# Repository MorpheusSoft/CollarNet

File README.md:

# 🐄 CollarNet / COWAI

**Ecosistema IoT Integral de Cerca Virtual, Telemetría Satelital y Monitoreo Ganadero en Tiempo Real**

---

## 📌 Descripción General

**CollarNet** (marca comercial **COWAI**) es una plataforma ganadera inteligente diseñada para entornos de campo y alta exigencia agropecuaria. Integra hardware IoT con geolocalización GNSS de alta precisión, comunicación celular 4G LTE, cercas virtuales poligonales dinámicas, acelerometría para monitoreo de actividad/rumia y una suite multiplataforma para técnicos y supervisores de finca.

---

## 🏗️ Arquitectura del Sistema

```
                   ┌──────────────────────────────────────────────┐
                   │               Collar IoT                     │
                   │    (ESP32-S3 + SIM7670G 4G LTE Digitel)     │
                   │  - GNSS Satelital (Lat/Lon en tiempo real)   │
                   │  - Algoritmo de Geocerca Ray-Casting Local   │
                   │  - Acelerómetro IMU (Reposo / Movimiento)    │
                   │  - Zumbador Piezoeléctrico (Alertas de Cerca)│
                   └──────────────────────┬───────────────────────┘
                                          │ MQTT (4G LTE Móvil)
                                          ▼
                   ┌──────────────────────────────────────────────┐
                   │             Broker MQTT Privado              │
                   │            (HiveMQ / Mosquitto)              │
                   └──────────────────────┬───────────────────────┘
                                          │
                                          ▼
┌─────────────────────────────────────────────────────────────────────────────────┐
│                          Servidor VPS en la Nube                                │
│                                                                                 │
│   ┌───────────────────────────┐         ┌───────────────────────────────────┐   │
│   │    Backend Node.js API    │◄───────►│    Base de Datos Espacial         │   │
│   │   - Express REST API      │         │    - PostgreSQL 16 + PostGIS      │   │
│   │   - Socket.io WebSockets  │         │    - Geometrías Hatos/Potreros    │   │
│   │   - Despacho de Alertas   │         │    - Histórico de Telemetría      │   │
│   └─────────────┬─────────────┘         └───────────────────────────────────┘   │
└─────────────────┼───────────────────────────────────────────────────────────────┘
                  │
     ┌────────────┴────────────┬────────────────────────┐
     ▼                         ▼                        ▼
┌──────────────┐      ┌──────────────────┐     ┌──────────────────┐
│  Dashboard   │      │    COWAI Ops     │     │   COWAI Campo    │
│  Web Central │      │  (App Técnico)   │     │ (App Supervisor) │
│ (React+Vite) │      │ (Android / PWA)  │     │ (Android / PWA)  │
└──────────────┘      └──────────────────┘     └──────────────────┘
```

---

## 🧩 Componentes del Repositorio

### 1. 📡 Firmware del Collar (`CollarNet.ino`, `config.h`)
* **Hardware**: Waveshare ESP32-S3 + módem celular SIM7670G 4G LTE.
* **Conectividad**: Comunicación celular fija (`NET_PREF_CELLULAR`) mediante APN `gprsweb.digitel.ve` con radio Wi-Fi apagada para máxima autonomía en campo abierto.
* **Seguridad de Ganado**: Cálculo de límites de potrero y hato directo en el collar por Ray-Casting; genera estímulos sonoros graduales (advertencia y peligro) si el animal se aproxima o supera el lindero.
* **Ahorro de Energía**: Transición a modo reposo cuando el acelerómetro no detecta movimiento.

### 2. 🖥️ Backend REST & WebSockets (`backend/`)
* Construido con Node.js y Express.
* Suscriptor MQTT que procesa telemetría en tiempo real y la retransmite a través de WebSockets (`socket.io`).
* Conexión a PostgreSQL con extensión espacial PostGIS para consultas geométricas avanzadas (`ST_Contains`, `ST_Distance`).
* Portal de descargas y servicio de aplicaciones PWA (`/descargas`, `/iphone`, `/apps/tecnico`, `/apps/finca`).

### 3. 🌐 Dashboard Web Central (`frontend/`)
* Aplicación de una sola página (SPA) desarrollada con React, Vite y TailwindCSS.
* Mapa satelital interactivo con capas Leaflet, trazado de geocercas, edición de vértices en vivo, monitoreo de collares y estado de batería.

### 4. 📱 Aplicaciones Móviles (`movil_ops/` y `movil_supervisor/`)
* Desarrolladas con **Flutter 3**.
* **COWAI Ops**: Herramienta de laboratorio y despliegue técnico (alta de hatos, escaneo de collares, diagnóstico GNSS/IMU).
* **COWAI Campo**: Herramienta de gestión ganadera (subdivisión de potreros, arreo en vivo, báscula Bluetooth y alertas sanitarias).
* Distribución disponible como instalador nativo Android (`.apk`) y Progressive Web App (`PWA`) optimizada para Safari en iOS.

---

## 🚀 Despliegue Rápido con Docker

El sistema de servidor está completamente contenedorizado para un despliegue inmediato:

```bash
# 1. Clonar el repositorio
git clone git@github.com:MorpheusSoft/CollarNet.git
cd CollarNet

# 2. Iniciar todos los servicios (Base de Datos PostGIS, Broker MQTT y Backend)
docker compose up -d --build
```

Los servicios quedarán disponibles en:
- **Dashboard Web & API**: `http://localhost:3500` (o `https://cowai.net` en producción)
- **Portal de Descargas Móviles**: `http://localhost:3500/descargas`
- **Broker MQTT**: puerto `1883`

---

## ⚡ Compilación y Flasheo del Firmware

Para compilar y grabar el firmware en el chip ESP32-S3 con `arduino-cli`:

```bash
# Compilar el sketch
arduino-cli compile --fqbn esp32:esp32:esp32s3 CollarNet.ino

# Subir al dispositivo físico conectado por USB (ejemplo en /dev/ttyACM4)
arduino-cli upload -p /dev/ttyACM4 --fqbn esp32:esp32:esp32s3 CollarNet.ino
```

---

## 📄 Licencia

Desarrollado para **CollarNet / COWAI** © 2026. Todos los derechos reservados.

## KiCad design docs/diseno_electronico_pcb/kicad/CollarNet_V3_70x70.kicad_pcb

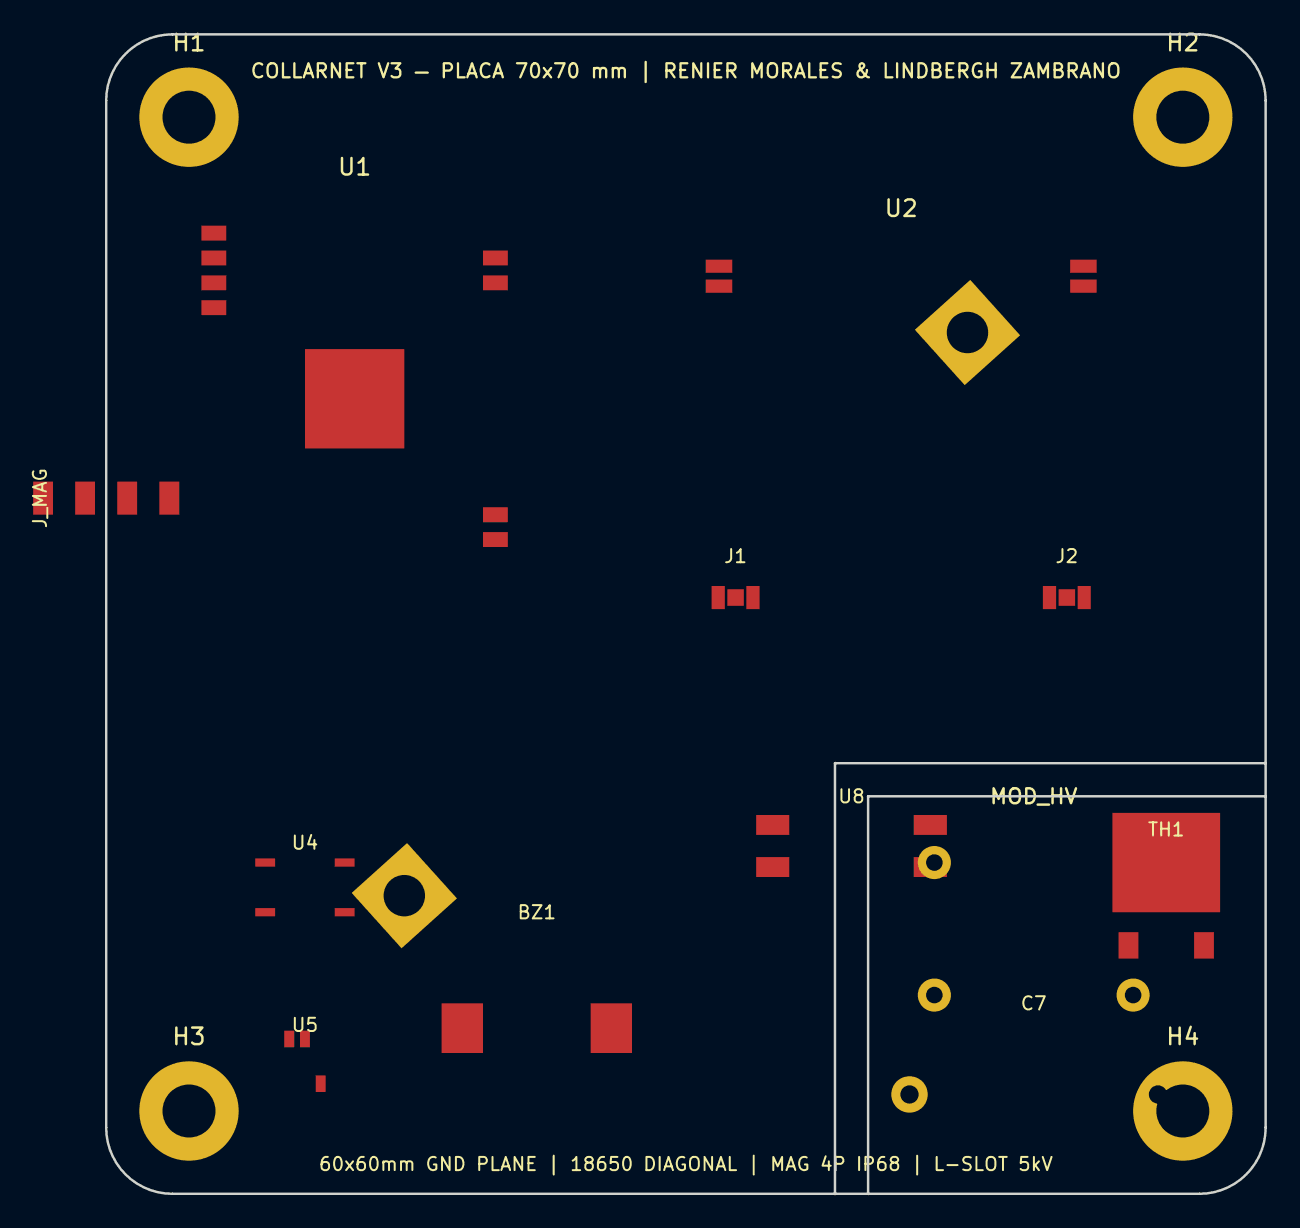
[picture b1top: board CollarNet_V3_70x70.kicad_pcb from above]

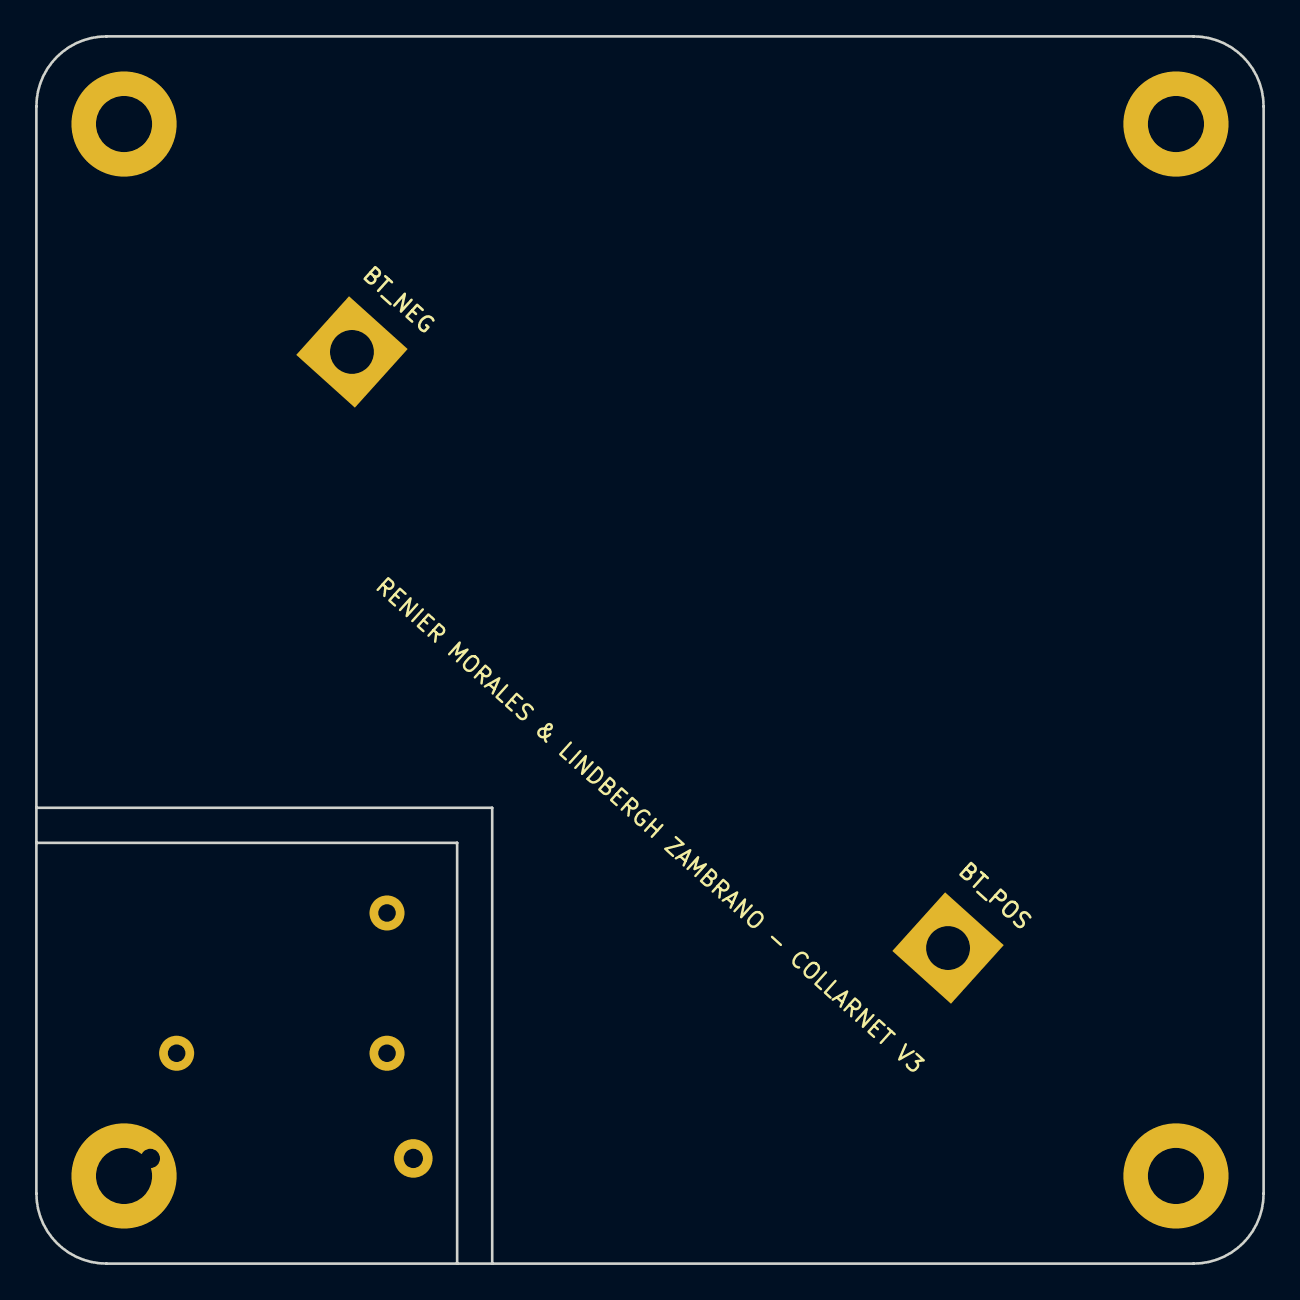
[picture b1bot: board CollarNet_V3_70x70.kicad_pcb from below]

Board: 2 copper layers, 70.0 x 70.0 mm, 18 parts (2 on the bottom side), 9 nets, no tracks yet.

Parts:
BT_NEG: BatteryHolder_Keystone_1048_1x18650
BT_POS: BatteryHolder_Keystone_1042_1x18650
BZ1: Buzzer_95dB; Buzzer_12x12mm_SMD
C7: 0.1uF 1000V CBB21; C_Rect_L18.0mm_W9.0mm_P15.00mm
H1, H2, H3, H4: MountingHole_3.2mm_M3_Pad
J1: U.FL_LTE; U.FL_Hirose_U.FL-R-SMT-1
J2: U.FL_GNSS; U.FL_Hirose_U.FL-R-SMT-1
J_MAG: MAG_4PIN_IP68; Magnetic_4Pin_Pogo_IP68
MOD_HV: Flyback_1000V; HV_Module_Flyback_1000V
TH1: TYN1225RG; TO-252-2
U1: ESP32-S3-WROOM-1-N16R8; ESP32-S3-WROOM-1
U2: SIM7670SA; SIMCom_SIM7670SA
U4: CN3791; SSOP-10_3.9x4.9mm_P1.00mm
U5: SY8089AAAC; SOT-23-5
U8: EL817C; SMDIP-4_W9.53mm

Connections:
+3.3V: U1.2, U5.1
BUZZER_PWM: BZ1.2, U1.4
GND: BT_NEG.1, H1.1, H2.1, H3.1, H4.1, J1.2, J1.3, J2.2, J2.3, J_MAG.4, U1.1, U1.41, U2.1, U4.4, U5.2, U8.2
HV_GND: C7.2, MOD_HV.2, U8.3
HV_PULSE: C7.1, MOD_HV.3, TH1.2
IMPULSE_TRIG: U1.3, U8.1
MODEM_RXD: J_MAG.2, U1.28, U2.16
MODEM_TXD: J_MAG.3, U1.27, U2.15
VBAT: BT_POS.1, BZ1.1, MOD_HV.1, U2.2, U4.7, U5.4

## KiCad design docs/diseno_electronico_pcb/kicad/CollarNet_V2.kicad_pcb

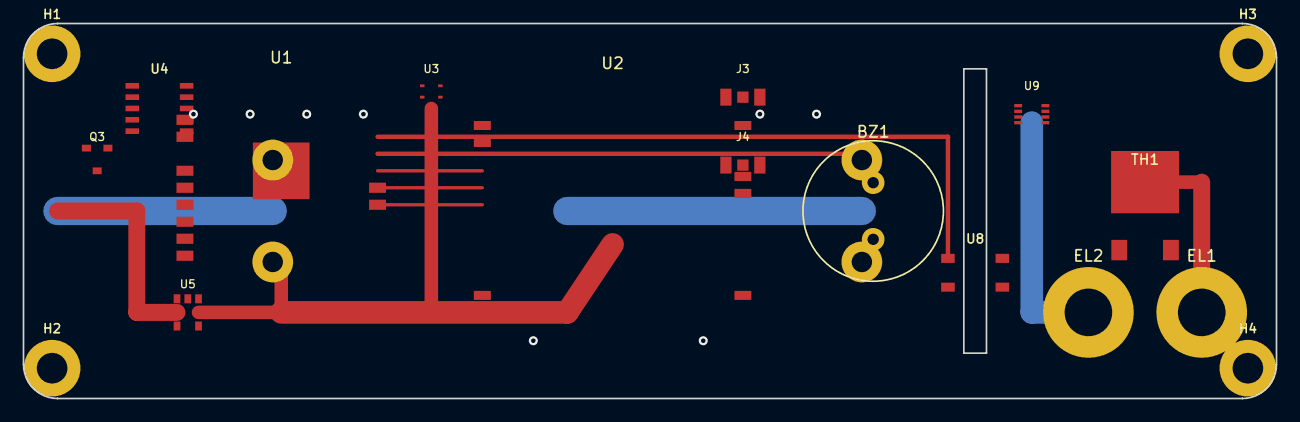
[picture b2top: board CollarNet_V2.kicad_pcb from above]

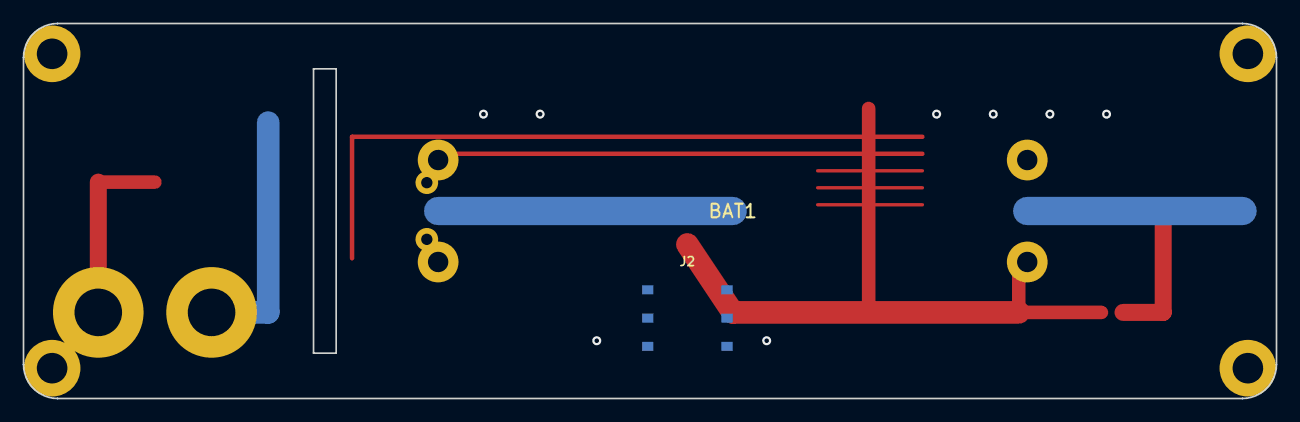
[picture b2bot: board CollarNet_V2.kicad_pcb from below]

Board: 2 copper layers, 110.6 x 33.1 mm, 20 parts (2 on the bottom side), 14 nets.

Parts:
BAT1: BatteryHolder_Keystone_1048_1x21700
BZ1: Buzzer_12x9.5RM7.6
EL1, EL2: MountingHole_4.2mm_M4_Pad
H1, H2, H3, H4: MountingHole_2.7mm_M2.5_Pad
J2: Nano_SIM_PushPull
J3, J4: U.FL_Hirose_U.FL-R-SMT-1
Q3: SOT-23
TH1: TO-252-2
U1: ESP32-S3-WROOM-1
U2: SIM7670SA-MNGV
U3: LGA-12_2x2mm
U4: SSOP-10_3.9x4.9mm_P1.00mm
U5: SOT-23-5
U8: SOP-4_4.4x3.9mm_P2.54mm
U9: VSSOP-8_2.3x2mm_P0.5mm

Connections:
+3.3V: U1.2, U1.3, U3.1, U5.3, U5.5
BUZZER_PWM: BZ1.2, U1.5
CN3791_DRV: Q3.1, U4.10
GND: BAT1.1, BAT1.2, H1.1, H2.1, H3.1, H4.1, J2.4, J3.2, J3.3, J4.2, J4.3, U1.1, U1.41, U2.2, U3.3, U4.2, U4.5, U5.2, U8.2
HV_GND: EL2.1, U8.3, U9.4
HV_PULSE: EL1.1, TH1.1, TH1.2
I2C_SCL: U1.9, U3.5
I2C_SDA: U1.8, U3.4
IMPULSE_TRIG: U1.4, U8.1, U9.2
MODEM_PWRKEY: U1.6, U2.1
MODEM_RXD: U1.18, U2.22
MODEM_TXD: U1.17, U2.21
SOLAR_IN: Q3.2, U4.6, U4.9
VBAT: BAT1.3, BAT1.4, BZ1.1, Q3.3, U2.38, U2.39, U4.7, U4.8, U5.1, U5.4, U8.4, U9.1, U9.3, U9.8

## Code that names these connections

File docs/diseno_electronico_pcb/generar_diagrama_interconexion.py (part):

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    bz_x = 580
    bz_y = 1710
    svg.append(draw_component_card(bz_x, bz_y, 340, 200, "BZ1 + Q1 + D4 (Buzzer 95dB)", "Bocina Acústica 4000Hz con Driver MOSFET", "C253457 / C20917", "#f97316", "BZ1 / Q1"))
    svg.append(draw_pin_item(bz_x, bz_y + 75, "G", "Q1 GATE", "BUZZER_PWM (ESP32 IO5)", align="left", net_color=c_trig))
    svg.append(draw_pin_item(bz_x, bz_y + 115, "D", "Q1 DRAIN", "Conectado a BZ1 (-) & D4", align="left", net_color=c_text_sub))
    svg.append(draw_pin_item(bz_x, bz_y + 155, "S", "Q1 SOURCE", "GND_SYS", align="left", net_color=c_gnd))
    svg.append(draw_pin_item(bz_x + 340, bz_y + 90, "+", "BZ1 (+)", "Alimentado desde VBAT", align="right", net_color=c_vbat))
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    q2_x = 1000
    q2_y = 1750
    svg.append(draw_component_card(q2_x, q2_y, 480, 160, "Q2 (AO3400A SOT-23)", "Driver N-MOSFET de Encendido Módem (PWRKEY)", "LCSC: C20917", "#a855f7", "Q2"))
    svg.append(draw_pin_item(q2_x, q2_y + 80, "1", "GATE", "MODEM_PWRKEY (Desde ESP32 IO6)", align="left", net_color=c_trig))
    svg.append(draw_pin_item(q2_x, q2_y + 120, "2", "SOURCE", "GND_SYS", align="left", net_color=c_gnd))
    svg.append(draw_pin_item(q2_x + 480, q2_y + 100, "3", "DRAIN", "Hacia U2 Pin 1 (PWRKEY activo LOW)", align="right", net_color=c_uart))

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    u8_h = 240
    svg.append(draw_component_card(u8_x, u8_y, u8_w, u8_h, "U8 (EL817S1C SOP-4)", "Optoacoplador de Barrera Galvánica (5,000V RMS)", "LCSC: C4999", "#f43f5e", "U8"))
    svg.append(f'<text x="{u8_x + 15}" y="{u8_y + 80}" font-family="sans-serif" font-size="11" font-weight="bold" fill="#38bdf8">LADO LÓGICO DIGITAL (ESP32)</text>')
    svg.append(draw_pin_item(u8_x, u8_y + 115, "1", "ANODE", "IMPULSE_TRIG (ESP32 IO4)", align="left", net_color=c_trig))
    svg.append(draw_pin_item(u8_x, u8_y + 165, "2", "CATHODE", "Retorno GND_SYS", align="left", net_color=c_gnd))

    svg.append(f'<text x="{u8_x + u8_w - 15}" y="{u8_y + 80}" font-family="sans-serif" font-size="11" font-weight="bold" fill="#f87171" text-anchor="end">LADO ALTA TENSIÓN (1000V)</text>')
    svg.append(draw_pin_item(u8_x + u8_w, u8_y + 115, "4", "COLLECTOR", "Disparo hacia U9 Watchdog", align="right", net_color=c_hv))
    svg.append(draw_pin_item(u8_x + u8_w, u8_y + 165, "3", "EMITTER", "Retorno Tierra HV_GND", align="right", net_color=c_hvgnd))

    # U9: 74LVC1G123DCK (Watchdog Hardware 1000ms)
    u9_x = 1600
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    svg.append(draw_pin_item(mod_x, mod_y + 90, "1", "IN (+)", "Alimentación desde VBAT", align="left", net_color=c_vbat))
    svg.append(draw_pin_item(mod_x, mod_y + 140, "2", "IN (-)", "Retorno Conmutado por Watchdog U9", align="left", net_color=c_gnd))
    svg.append(draw_pin_item(mod_x + mod_w, mod_y + 90, "3", "HV_OUT (+)", "Alta Tensión +1000V DC -> C7 & TH1", align="right", net_color=c_hv))
    svg.append(draw_pin_item(mod_x + mod_w, mod_y + 140, "4", "HV_GND (-)", "Retorno Masa Aislada HV_GND", align="right", net_color=c_hvgnd))

    # C7: Condensador CDI 0.1uF 1000V CBB21
    c7_x = 2110
    c7_y = 1460
    svg.append(draw_component_card(c7_x, c7_y, 460, 200, "C7 (0.1µF 1000V CBB21)", "Condensador Polipropileno Metalizado (Energía: 50 mJ)", "LCSC: C2839151", "#b91c1c", "C7"))
    svg.append(draw_pin_item(c7_x, c7_y + 80, "1", "HV_POS", "+1000V DC (Almacén de Energía CDI)", align="left", net_color=c_hv))
    svg.append(draw_pin_item(c7_x + 460, c7_y + 80, "2", "HV_NEG", "Retorno Masa Aislada HV_GND", align="right", net_color=c_hvgnd))
    svg.append(draw_pin_item(c7_x, c7_y + 130, "R_BLEED", "10MΩ / 1kV", "Resistencia de Sangrado de Seguridad", align="left", net_color=c_text_sub))

    # TH1 (Tiristor TYN1225RG) + D6 (DB3 Diac)
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    el_h = 300
    svg.append(draw_component_card(el_x, el_y, el_w, el_h, "EL1 & EL2 (BORNES M4 INOX)", "Contactos Bipolares Dérmicos (Inox 316 Calidad Marina)", "PAD-M4-8MM", "#ef4444", "EL1 EL2"))
    svg.append(draw_pin_item(el_x, el_y + 95, "EL1", "PULSE (+)", "Salida Pulso Choque CDI (+1000V)", align="left", net_color=c_hv))
    svg.append(draw_pin_item(el_x, el_y + 165, "EL2", "RETURN (-)", "Retorno Galvánico hacia HV_GND", align="left", net_color=c_hvgnd))
    svg.append(draw_pin_item(el_x, el_y + 225, "R_LIM", "220Ω / 2W", "Limitador de Corriente Anti-Quemaduras", align="left", net_color=c_text_accent))

    # Resumen de Seguridad de la Etapa HV
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      <path d="M {u1_x} {u1_y + 575} C {u1_x - 100} {u1_y + 575}, {u3_x + 440} {u3_y + 80}, {u3_x + 380} {u3_y + 80}" fill="none" stroke="{c_i2c}" stroke-width="2.5"/>
    ''')

    # IMPULSE_TRIG (U1 IO4 -> U8 EL817 Pin 1)
    svg.append(f'''
      <path d="M {u1_x + u1_w} {u1_y + 440} C {u1_x + u1_w + 300} {u1_y + 440}, {u8_x - 100} {u8_y + 115}, {u8_x} {u8_y + 115}" fill="none" stroke="{c_trig}" stroke-width="3"/>
    ''')
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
